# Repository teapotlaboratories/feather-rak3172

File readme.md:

# Teapotlabs Feather RAK3172

Teapotlabs Feather RAK3172 a Low-cost, Low-power LoRaWAN development board that breaks out [RAKwireless RAK3172](https://docs.rakwireless.com/Product-Categories/WisDuo/RAK3172-Module/Datasheet) to an Adafruit Feather-compatible format.

Based on the RAK3172, a STM32WLE5CC based module with ARM Cortex M4 processor, 48 MHz and 3.3V logic. The chip has a 256K of flash and 64K of RAM. 
With low-power application in mind, the board is capable to be in sleep mode for as low as 11uA, it also has a built-in voltage divider to sense battery voltage and battery charger.

Teapotlabs Feather RAK3172 is heavily inspired by [Penguino STM32WL LoRa-E5](https://github.com/azerimaker/Penguino-STM32WL-LoRa-E5) and [BastWAN-WLE](https://github.com/ElectronicCats/BastWAN-WLE) projects!

## Specification

- [RAK3172](https://docs.rakwireless.com/Product-Categories/WisDuo/RAK3172-Module/Overview/): An STM32WLE5CC module
- 3.3V only power/pin. 
- Down to 11uA Deep-Sleep
- Switchable TX Power. 14 dBm or 22 dBm on 915MHz frequency
- Supports LoRaWAN 1.0.3
- USB-C for **Arduino** and  **Mbed OS/STM32Cube** programming
- SMA antenna connector 
- JST-PH 2-Pin Battery Connector
- Built-in LiPo Charger ( 200mA Charge Rate )
- Voltage-Divider for Battery Monitoring ( default: **disabled** )
- LED Indicator on pin 8 ( default: **disabled** )
- Compatible with many Adafruit FeatherWings
- Max 1A power output

## To-do
- Update assembly/TeapotFeatherRAK3172_Assembly.zip and docs file to Revision 9.1

## Schematics

### Jumper Definition
- JP1 and JP4: Enable/Disable Voltage Divider for Battery Sensing
- JP2: Enable/Disable LED Indicator on Pin 8
- JP3, JP5, and JP6: Enable/Disable UART Bridge

### Revision
- Revision 9  : First public release
- Revision 9.1: Fix LED D1 polarity 

### Pinout Diagram
> :warning: **The following pinout is not complete, please see STM32WLE5CC datasheet for more details.** 

## Board
<p align="center">  <br><b>PCB Render</b></p>

Built using KiCAD, the board is design to be as small as possible. The following design are based on the latest revision.
| Top Board | Bottom Board |
|--|--|
|  |  |
|  |  |

 <p align="center"> <br><b>PCB Top and Bottom Layout</b></p> 
  
### Case

The case is design by [atmakers](https://www.thingiverse.com/atmakers/designs) with **Attribution-ShareAlike 3.0 Unported (CC BY-SA 3.0)** license.
The cases are 3D printable with any generic 3D printer with/without suppport (depends on the orientation). The STL files are available from authors download page  [here](https://www.thingiverse.com/thing:3212895) or from [this](https://github.com/teapotlaboratories/feather-rak3172/tree/main/hardware/case) repo.
 <p align="center"><br><b>Case Open</b></p>
 
### Measurement
Power consumption measured using [Nordic PPK2](https://www.nordicsemi.com/Products/Development-hardware/Power-Profiler-Kit-2). The following are the summary of the measurement:
- Sleep and all jumper disabled (JP1 - JP6): **10.44 uA**
- Sleep and UART-Bridge enabled ( JP3, JP5, and JP6 ): **23.76 uA**
- Sleep, UART-Bridge and Battery Sense enabled ( JP1, and JP3 - JP6 ): **25.41 uA** 
- Transmit at 14 dBm: **40.45 mA**
- Transmit at 20 dBm: **100.38 mA**

More detailed measurement can be found [here](https://github.com/teapotlaboratories/feather-rak3172/tree/main/docs/measurement)

### Bill Of Materials
Most of the components are generic and can be bought from any electornics/semi-conductor distributor. RAK3172 is the only component available in [RAKwireless store](https://store.rakwireless.com/products/wisduo-lpwan-module-rak3172?variant=40014759493830). The bill of materials can be downloaded [here](https://github.com/teapotlaboratories/feather-rak3172/raw/main/hardware/bill_of_materials.csv)

> :warning: **Be sure to buy the RAK3172 variant without IPEX to use SMA connector** 

|Id|Designator|Quantity|Value|Footprint|
|:----|:----|:----|:----|:----|
|1|C11,C7,C4,C1|4|100n|0603_1608Metric|
|2|C6,C3|2|10u|0603_1608Metric|
|3|C9,C8,C10|3|10u|0805_2012Metric|
|4|D1|1|BLUE|0603_1608Metric|
|5|D2|1|ORANGE|0603_1608Metric|
|6|D3|1|B5819W|SOD-123|
|7|J3|1|U262-161N-4BVC11|USB_C_Receptacle_XKB_U262-16XN-4BVC11|
|8|J4|1|SMA-KE-P903|SMA-KE-P903|
|9|J6|1|S2B-PH-SM4-TB|JST_PH_S2B-PH-SM4-TB_1x02-1MP_P2.00mm_Horizontal|
|10|L1|1|0|0402_1005Metric|
|11|Q1|1|DMG3415UQ-7|SOT-23|
|12|R10|1|10M|0603_1608Metric|
|13|R2,R6,R1|3|1k|0603_1608Metric|
|14|R3,R5,R4|3|5.1k|0603_1608Metric|
|15|R7,R8|2|10k|0603_1608Metric|
|16|R9|1|4.7M|0603_1608Metric|
|17|SW1|1|B3U-1000P|SW_SPST_B3U-1000P|
|18|SW2|1|B3U-1000P|SW_SPST_B3U-1000P|
|19|U1|1|RAK3172|RAK3172|
|20|U2|1|CH340E|MSOP-10_3x3mm_P0.5mm|
|21|U3|1|MCP73831T-2ACI/OT|SOT-23-5|
|22|U4|1|XC6220B331MR-G|SOT-23-5|
|23|C5,C2|2|DNP|0402_1005Metric|
|24|J2|1|DNP|PinHeader_1x12_P2.54mm_Vertical|
|25|J1|1|DNP|PinHeader_1x16_P2.54mm_Vertical|

## Programming

By default, programming the device can be done over  the **USB-C**. Internally, the USB-C connects to the UART-Bridge that connects to the **UART2** port of the RAK3172. Out of the factory, the RAK3172 chip ships with an **AT firmware** that can be tested by sending AT command via the USB-C.

Using the USB-C, user can program the board using the **Arduino** or **MbedOS/STM32Cube** SDK.
The following are some very good tutorial to start developing with the device:
 - [Communicating with the AT firmware](https://docs.rakwireless.com/Product-Categories/WisDuo/RAK3172-Module/Quickstart/#rak3172-as-a-lora-lorawan-modem-via-at-command)
 - [Programming with Arduino](https://docs.rakwireless.com/Product-Categories/WisDuo/RAK3172-Module/Quickstart/#rak3172-as-a-stand-alone-device-using-rui3)
 - [Programming with STM32Cube](https://docs.rakwireless.com/Product-Categories/WisDuo/RAK3172-Module/Low-Level-Development/#rak3172-on-stm32cubeide-with-stm32wl-sdk-v1-0-0)
	 - RAKDAP1 is not needed. Before connecting to **STM32CubeProgrammer**, hold `BOOT` and press `RESET` on the board, to boot to UART bootloader of the RAK3172. After `RESET` button is pressed, `BOOT` button can be released, and the board should be able to connect to the **STM32CubeProgrammer**
 - [Programming with MbedOS](https://github.com/hallard/LoRa-E5-Tiny/blob/main/README.md#compile-and-flash-firmware)
	 - Programming the board can be done **without** using the ST-LINK, it should be simillar to [Programming with STM32Cube](https://docs.rakwireless.com/Product-Categories/WisDuo/RAK3172-Module/Low-Level-Development/#rak3172-on-stm32cubeide-with-stm32wl-sdk-v1-0-0) process.

## Example Project
Teapotlabs Feather RAK3172 is a feather compatible board, and hence is compatible with the many available FeatherWing. The following are some example project that uses FeatherWings.

### Over-engineered Clock 
An over-engineered clock with main purpose to showcase FeatherWings compatibility.
FeatherWings and sensors used:  
- [Ultimate GPS](adafruit.com/product/3133)  
- [Tri-Color E-Ink](adafruit.com/product/4814)  
- [Qwiic Shield](sparkfun.com/products/16790)  
- [BME680](adafruit.com/product/3660)  
- [Modified E-Ink Case](learn.adafruit.com/eink-featherwing-display-stand)

<p align="center">

<br><b>Front and Side View</b></p>

<p align="center">  

<br><b>Back View</b>
</p>
 
## Reference
The project won't be possible without the amazing work from people across the globe. The following are the reference to those awesome projects:

 - [Adafruit Feather RP2040](https://github.com/adafruit/Adafruit-Feather-RP2040-PCB)
 - [Penguino STM32WL LoRa-E5](https://github.com/azerimaker/Penguino-STM32WL-LoRa-E5)
 - [BastWAN-WLE](https://github.com/ElectronicCats/BastWAN-WLE)

## License
The product is open-source! However, some part of library used under **src**, might have it's own license.
Please reach out or create a ticket to report any license violation.

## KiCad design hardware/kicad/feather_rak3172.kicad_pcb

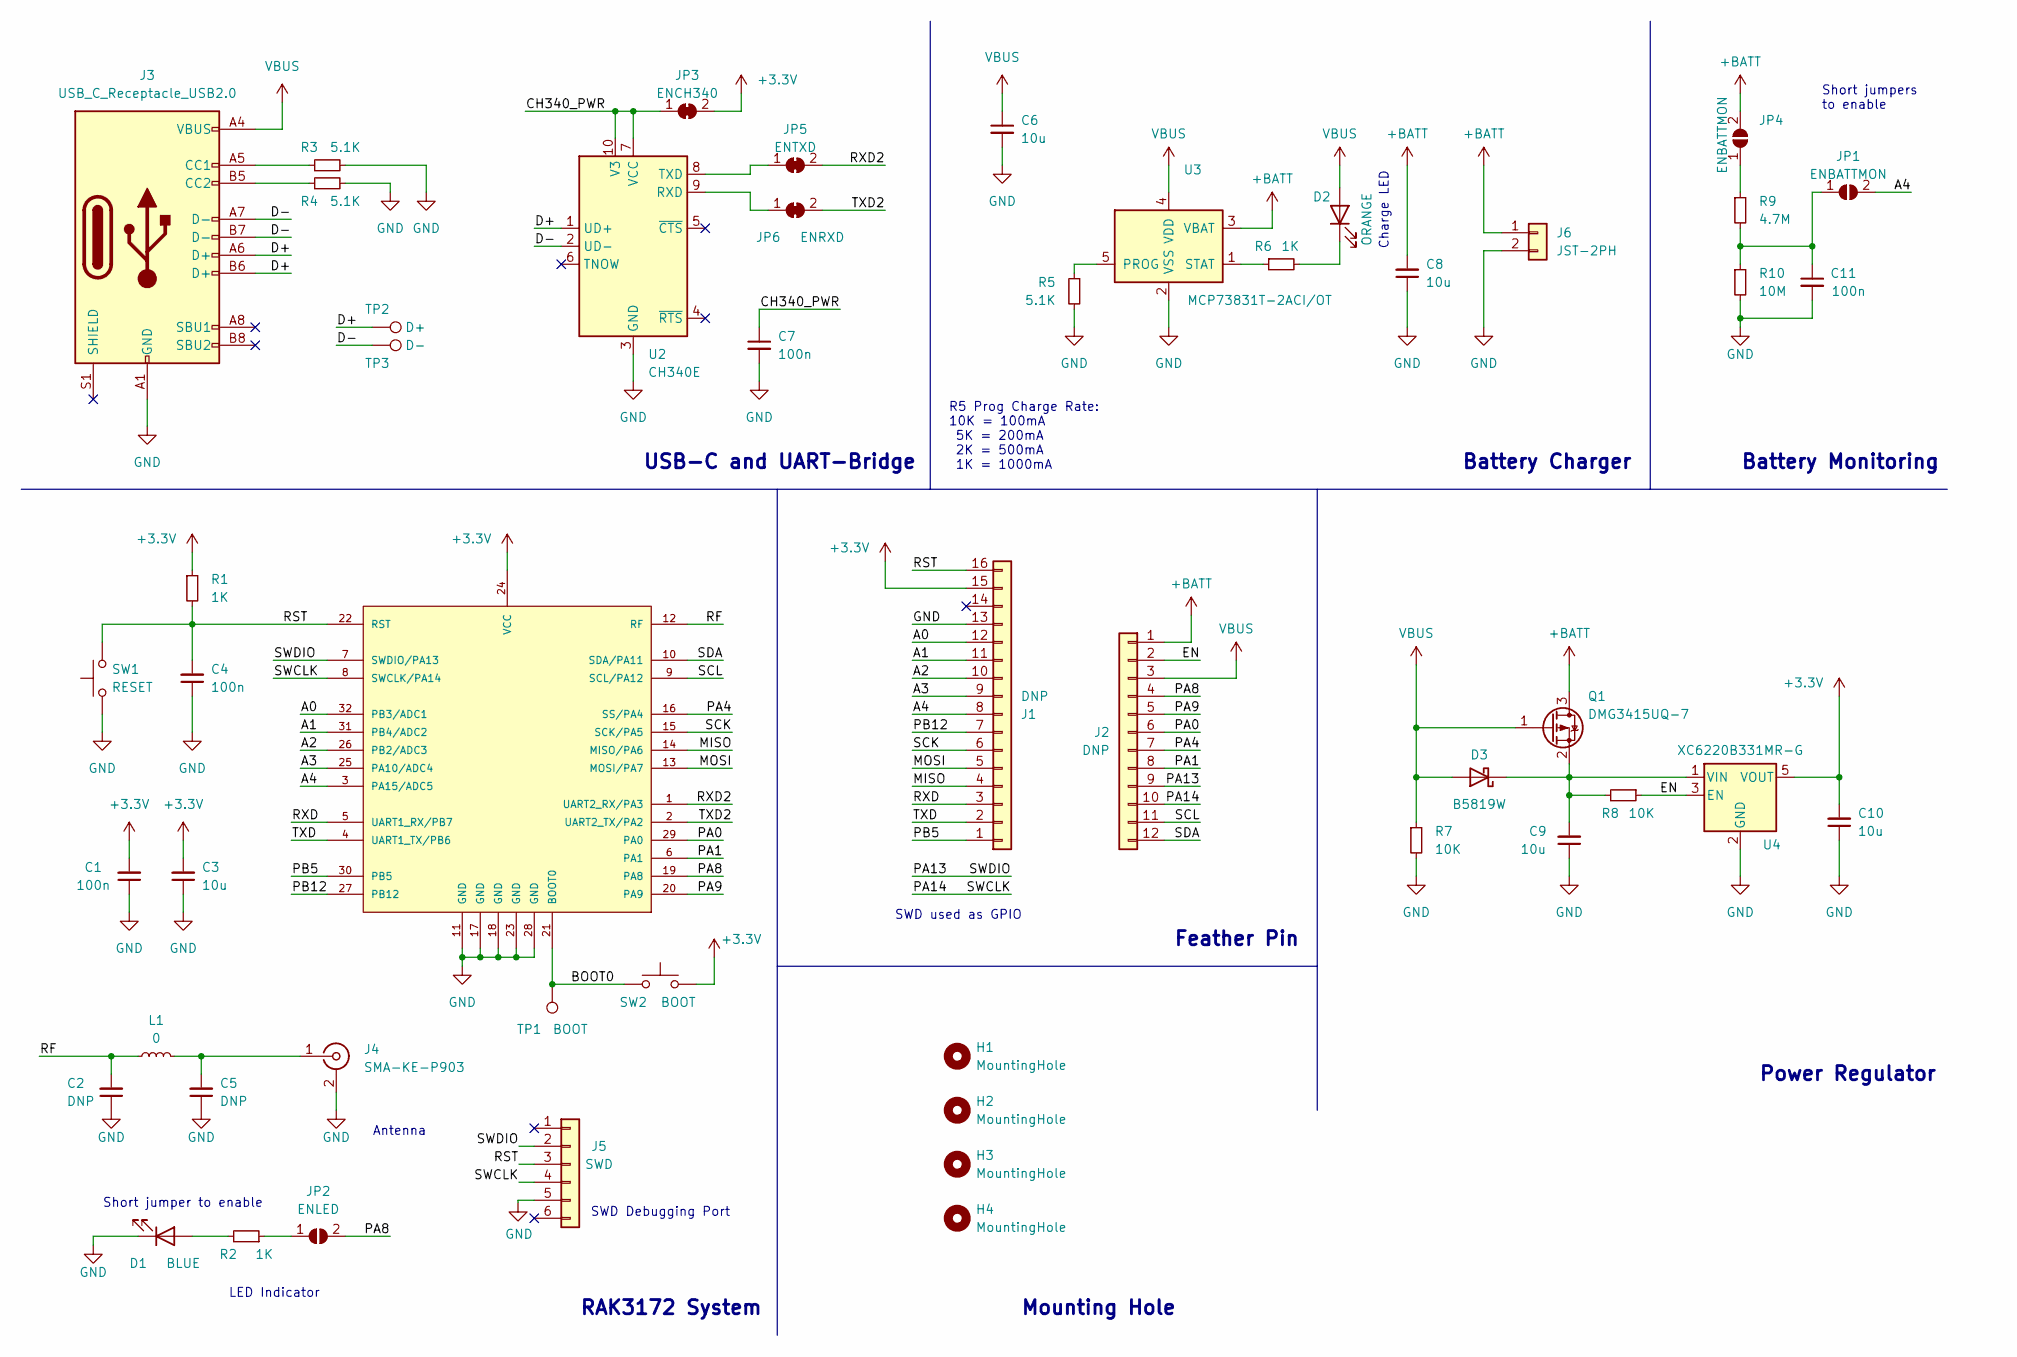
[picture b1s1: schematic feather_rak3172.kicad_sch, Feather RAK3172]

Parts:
C1, C4, C7, C11: 100n; C_0603_1608Metric; Part Description Ceramic Capacitor 100nF 10% 10V X7R
C2, C5: DNP; C_0402_1005Metric
C3, C6: 10u; C_0603_1608Metric; Part Description Ceramic Capacitor 10uF 10% 10V X5R
C8, C9, C10: 10u; C_0805_2012Metric; Part Description Ceramic Capacitor 10uF 10% 10V X5R
D1: BLUE; LED_0603_1608Metric; Part Description Blue 2V 25mA
D2: ORANGE; LED_0603_1608Metric; Part Number Orange 2V 25mA
D3: B5819W; D_SOD-123; Part Description 0.05mA@40V 0.58V@1A
H1, H2, H3, H4: MountingHole; MountingHole_2.5mm
J1: DNP; PinHeader_1x16_P2.54mm_Vertical
J2: DNP; PinHeader_1x12_P2.54mm_Vertical
J3: USB_C_Receptacle_USB2.0; USB_C_Receptacle_XKB_U262-16XN-4BVC11; Part Number U262-161N-4BVC11
J4: SMA-KE-P903; Part Number SMA-KE-P903
J5: SWD; Tag-Connect_TC2030-IDC-NL_2x03_P1.27mm_Vertical
J6: JST-2PH; JST_PH_S2B-PH-SM4-TB_1x02-1MP_P2.00mm_Horizontal; Part Number JST-PH S2B-PH-SM4-TB
JP1, JP4: ENBATTMON; SolderJumper-2_P1.3mm_Open_RoundedPad1.0x1.5mm
JP2: ENLED; SolderJumper-2_P1.3mm_Open_RoundedPad1.0x1.5mm
JP3: ENCH340; SolderJumper-2_P1.3mm_Bridged_RoundedPad1.0x1.5mm
JP5: ENTXD; SolderJumper-2_P1.3mm_Bridged_RoundedPad1.0x1.5mm
JP6: ENRXD; SolderJumper-2_P1.3mm_Bridged_RoundedPad1.0x1.5mm
L1: 0; L_0402_1005Metric
Q1: DMG3415UQ-7; SOT-23; Part Number DMG3415UQ-7
R1, R2, R6: 1K; R_0603_1608Metric; Part Description Resistor 1k 5% 100mW
R3, R4: 5.1K; R_0603_1608Metric; Part Description Resistor 5.1K 1% 100mW
R5: 5.1K; R_0603_1608Metric; Part Description Resistor 5.1k 1% 100mW
R7, R8: 10K; R_0603_1608Metric; Part Description Resistor 10k 5% 100mW
R9: 4.7M; R_0603_1608Metric; Part Description Resistor 4.7M 1% 100mW
R10: 10M; R_0603_1608Metric; Part Description Resistor 10M 1% 100mW
SW1: RESET; SW_SPST_B3U-1000P; Part Number B3U-1000P
SW2: BOOT; SW_SPST_B3U-1000P; Part Number B3U-1000P
TP1: BOOT; TestPoint_Pad_D1.0mm
TP2: D+; TestPoint_Pad_D1.0mm
TP3: D-; TestPoint_Pad_D1.0mm
U1: RAK3172; Part Number RAK3172
U2: CH340E; MSOP-10_3x3mm_P0.5mm; Part Number CH340E
U3: MCP73831T-2ACI/OT; SOT-23-5; Part Number MCP73831T-2ACI/OT
U4: XC6220B331MR-G; SOT-23-5; Part Number XC6220B331MR-G

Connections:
+3.3V: C1.2, C3.2, C10.2, J1.15, JP3.2 (B), R1.1, SW2.1, U1.24 (VCC), U4.5 (VOUT)
+BATT: C8.2, J2.1, J6.1, JP4.2 (B), Q1.3 (D), U3.3 (VBAT)
/A0: J1.12, U1.32 (PB3/ADC1)
/A1: J1.11, U1.31 (PB4/ADC2)
/A2: J1.10, U1.26 (PB2/ADC3)
/A3: J1.9, U1.25 (PA10/ADC4)
/A4: J1.8, JP1.2 (B), U1.3 (PA15/ADC5)
/BOOT0: SW2.2, TP1.1, U1.21 (BOOT0)
/CH340_PWR: C7.1, JP3.1 (A), U2.7 (VCC), U2.10 (V3)
/D+: J3.A6 (D+), J3.B6 (D+), TP2.1, U2.1 (UD+)
/D-: J3.A7 (D-), J3.B7 (D-), TP3.1, U2.2 (UD-)
/EN: J2.2, R8.1, U4.3 (EN)
/MISO: J1.4, U1.14 (MISO/PA6)
/MOSI: J1.5, U1.13 (MOSI/PA7)
/PA0: J2.6, U1.29 (PA0)
/PA1: J2.8, U1.6 (PA1)
/PA4: J2.7, U1.16 (SS/PA4)
/PA8: J2.4, JP2.2 (B), U1.19 (PA8)
/PA9: J2.5, U1.20 (PA9)
/PA13: J2.9, J5.2, U1.7 (SWDIO/PA13)
/PA14: J2.10, J5.4, U1.8 (SWCLK/PA14)
/PB5: J1.1, U1.30 (PB5)
/PB12: J1.7, U1.27 (PB12)
/RF: C2.2, L1.1, U1.12 (RF)
/RST: C4.2, J1.16, J5.3, R1.2, SW1.2, U1.22 (RST)
/RXD: J1.3, U1.5 (UART1_RX/PB7)
/RXD2: JP5.2 (B), U1.1 (UART2_RX/PA3)
/SCK: J1.6, U1.15 (SCK/PA5)
/SCL: J2.11, U1.9 (SCL/PA12)
/SDA: J2.12, U1.10 (SDA/PA11)
/TXD: J1.2, U1.4 (UART1_TX/PB6)
/TXD2: JP6.2 (B), U1.2 (UART2_TX/PA2)
GND: C1.1, C2.1, C3.1, C4.1, C5.1, C6.2, C7.2, C8.1, C9.1, C10.1, C11.2, D1.1 (K), J1.13, J3.A1 (GND), J3.A12 (GND), J3.B1 (GND), J3.B12 (GND), J4.2 (Ext), J5.5, J6.2, R3.2, R4.2, R5.2, R7.2, R10.2, SW1.1, U1.11 (GND), U1.17 (GND), U1.18 (GND), U1.23 (GND), U1.28 (GND), U2.3 (GND), U3.2 (VSS), U4.2 (GND)
unnamed: C5.2, J4.1 (In), L1.2
unnamed: C9.2, D3.1 (K), Q1.2 (S), R8.2, U4.1 (VIN)
unnamed: C11.1, JP1.1 (A), R9.2, R10.1
unnamed: D2.1 (K), R6.2
unnamed: J3.A5 (CC1), R3.1
unnamed: J3.B5 (CC2), R4.1
unnamed: JP2.1 (A), R2.1
unnamed: JP4.1 (A), R9.1
unnamed: JP5.1 (A), U2.8 (TXD)
unnamed: JP6.1 (A), U2.9 (RXD)
unnamed: D1.2 (A), R2.2
unnamed: R5.1, U3.5 (PROG)
unnamed: R6.1, U3.1 (STAT)
VBUS: C6.1, D2.2 (A), D3.2 (A), J2.3, J3.A4 (VBUS), J3.A9 (VBUS), J3.B4 (VBUS), J3.B9 (VBUS), Q1.1 (G), R7.1, U3.4 (VDD)

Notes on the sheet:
Charge LED
Battery Monitoring
RAK3172 System
SWD used as GPIO
Mounting Hole
R5 Prog Charge Rate: 10K = 100mA 5K = 200mA 2K = 500mA 1K = 1000mA
Short jumpers to enable
Short jumper to enable
USB-C and UART-Bridge
SWD Debugging Port
LED Indicator
Antenna
Power Regulator
Battery Charger
Feather Pin

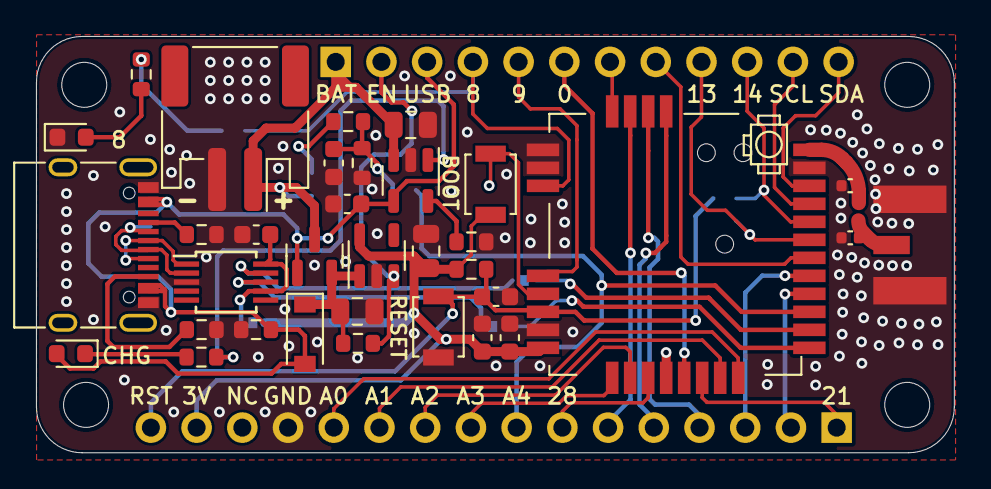
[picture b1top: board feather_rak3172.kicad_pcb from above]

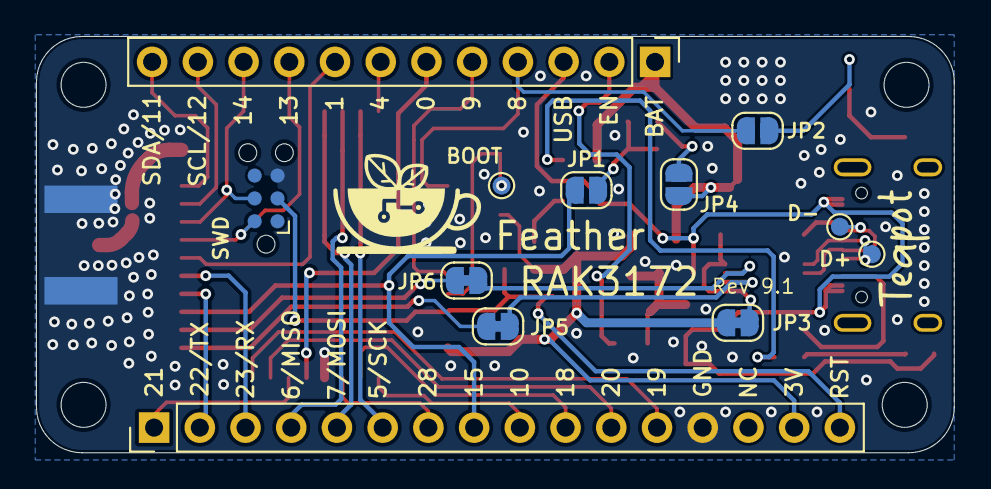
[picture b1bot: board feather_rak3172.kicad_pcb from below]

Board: 2 copper layers, 51.0 x 23.1 mm, 51 parts (12 on the bottom side), 47 nets.

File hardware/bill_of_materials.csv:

Id,Designator,Quantity,Manufacturer,Manufacturer Part Number,Value,Description,Footprint,Type,Distributor,Distributor Part Number,Distributor Link
1,"C11,C7,C4,C1",4,YAGEO,CC0603KRX7R6BB104,100n,Ceramic Capacitor 100n 10% 10V X7R,0603_1608Metric,SMD,LCSC,C519438,https://www.lcsc.com/product-detail/_YAGEO-_C519438.html
2,"C6,C3",2,Samsung Electro-Mechanics,CL10A106KP8NNNC,10u,Ceramic Capacitor 10u 10% 10V X5R,0603_1608Metric,SMD,LCSC,C19702,https://www.lcsc.com/product-detail/_Samsung-Electro-Mechani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
3,"C9,C8,C10",3,Samsung Electro-Mechanics,CL21A106KPFNNNE,10u,Ceramic Capacitor 10u 10% 10V X5R,0805_2012Metric,SMD,LCSC,C17024,https://www.lcsc.com/product-detail/_Samsung-Electro-Mechani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
4,D1,1,Everlight Elec,19-217/BHC-ZL1M2RY/3T,BLUE,LED Blue 2V 25mA,0603_1608Metric,SMD,LCSC,C72041,https://www.lcsc.com/product-detail/_Everlight-Elec-_C72041.html
5,D2,1,EKINGLUX,E6C0603SEAC1UDA,ORANGE,LED Orange 2V 25mA,0603_1608Metric,SMD,LCSC,C375450,https://www.lcsc.com/product-detail/_EKINGLUX-_C375450.html
6,D3,1,GOODWORK,B5819W,B5819W,Schottky Barrier Diodes (SBD) 40V 0.58V@1A,SOD-123,SMD,LCSC,C2943878,https://www.lcsc.com/product-detail/_GOODWORK-_C2943878.html
7,J3,1,XKB Connectivity,U262-161N-4BVC11,U262-161N-4BVC11,USB Type C Receptacle,USB_C_Receptacle_XKB_U262-16XN-4BVC11,SMD,LCSC,C319148,https://www.lcsc.com/product-detail/_XKB-Connectivity-_C319148.html
8,J4,1,DreamLNK,SMA-KE-P903,SMA-KE-P903,SMA RF Connectors Board Edge 50Ω 5.35mm 915MHz ,SMA-KE-P903,Through-Hole,LCSC,C914558,https://www.lcsc.com/product-detail/_DreamLNK-_C914558.html
9,J6,1,JST Sales America Inc.,S2B-PH-SM4-TB(LF)(SN),S2B-PH-SM4-TB,"Connector Header Right Angle 2 position 0.079"" (2.00mm)",JST_PH_S2B-PH-SM4-TB_1x02-1MP_P2.00mm_Horizontal,SMD,LCSC,C295747,https://www.lcsc.com/product-detail/Wire-To-Board-Wire-To-Wi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
10,L1,1,YAGEO,RC0402JR-070RL,0,Resistor 0 5% 65mW,0402_1005Metric,SMD,LCSC,C60485,https://www.lcsc.com/product-detail/_YAGEO-_C60485.html
11,Q1,1,Diodes Incorporated,DMG3415UQ-7,DMG3415UQ-7,MOSFET P-Channel 20V 4A 39mΩ@4.5V,SOT-23,SMD,LCSC,C459537,https://www.lcsc.com/product-detail/_Diodes-Incorporated-_C4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
12,R10,1,UNI-ROYAL(Uniroyal Elec),0603WAF1005T5E,10M,Resistor 10M 1% 100mW,0603_1608Metric,SMD,LCSC,C7250,https://www.lcsc.com/product-detail/_UNI-ROYAL-Uniroyal-Elec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
13,"R2,R6,R1",3,FOJAN,FRC0603J102 TS,1k,Resistor 1k 5% 100mW,0603_1608Metric,SMD,LCSC,C2907113,https://www.lcsc.com/product-detail/_FOJAN-_C2907113.html
14,"R3,R5,R4",3,YAGEO,RC0603FR-075K1L,5.1k,Resistor 5.1k 1% 100mW,0603_1608Metric,SMD,LCSC,C105580,https://www.lcsc.com/product-detail/_YAGEO-_C105580.html
15,"R7,R8",2,YAGEO,RC0603JR-0710KL,10k,Resistor 10k 5% 100mW,0603_1608Metric,SMD,LCSC,C99198,https://www.lcsc.com/product-detail/_YAGEO-_C99198.html
16,R9,1,UNI-ROYAL(Uniroyal Elec),0603WAF4704T5E,4.7M,Resistor 4.7M 1% 100mW,0603_1608Metric,SMD,LCSC,C23163,https://www.lcsc.com/product-detail/_UNI-ROYAL-Uniroyal-Elec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
17,SW1,1,Omron Electronics,B3U-1000P,B3U-1000P,Tactile Switches SPST 50mA 12V 2.5x3mm,SW_SPST_B3U-1000P,SMD,LCSC,C231329,https://www.lcsc.com/product-detail/_Omron-Electronics-_C231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
18,SW2,1,Omron Electronics,B3U-1000P,B3U-1000P,Tactile Switches SPST 50mA 12V 2.5x3mm,SW_SPST_B3U-1000P,SMD,LCSC,C231329,https://www.lcsc.com/product-detail/_Omron-Electronics-_C231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
19,U1,1,RAKwireless,RAK3172,RAK3172,RAK3172 Module without IPEX AS923,RAK3172,SMD,RAKwireless,309044,Contact inquiry@rakwireless.com for SKU: 309044
20,U2,1,WCH(Jiangsu Qin Heng),CH340E,CH340E,USB to UART IC 2Mbps Transceiver USB 2.0,MSOP-10_3x3mm_P0.5mm,SMD,LCSC,C99652,https://www.lcsc.com/product-detail/_WCH-Jiangsu-Qin-Heng-_C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
21,U3,1,Microchip Technology,MCP73831T-2ACI/OT,MCP73831T-2ACI/OT,Charger IC Lithium Ion/Polymer,SOT-23-5,SMD,LCSC,C424093,https://www.lcsc.com/product-detail/Battery-Management-ICs_M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
22,U4,1,Torex Semiconductor,XC6220B331MR-G,XC6220B331MR-G,Linear Voltage Regulators (LDO) 1A Fixed +3.3V,SOT-23-5,SMD,LCSC,C86534,https://www.lcsc.com/product-detail/_Torex-Semicon-_C86534.html
23,"C5,C2",2,-,-,DNP,Do Not Populate,0402_1005Metric,DNP,-,-,-
24,J2,1,-,-,DNP,Do Not Populate,PinHeader_1x12_P2.54mm_Vertical,DNP,-,-,-
25,J1,1,-,-,DNP,Do Not Populate,PinHeader_1x16_P2.54mm_Vertical,DNP,-,-,-

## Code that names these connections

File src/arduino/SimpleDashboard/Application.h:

#ifndef TEAPOT_APPLICATION_H
#define TEAPOT_APPLICATION_H

#include "Arduino.h"
#include "Adafruit_BME680.h"
#include "TinyGPSPlus.h"

// configuration for teapot bwlr3d application
#include "Configuration.h"

/* pin definition */
#define BLUE_LED      PA8
//#define GPS_ENABLE            nullptr
//#define GPS_RESET            nullptr
#define BATT_MEASURE  PA15
#define GPS_TXD       PB7
#define GPS_RXD       PB6
#define I2C_SDA       PA11
#define I2C_SCL       PA12

#ifndef ADC_TO_BATTERY
  #error "ADC_TO_BATTERY not set"
#endif

/* application definition */
namespace teapot{
  enum class ReturnCode {
    kOk = 0,
    kError,
    kBme68xNotFound,
    kBme68xReadFail,
    kPeripheralOff,
    kTimeout,
  };
  
  enum class Sensor : uint32_t {
    kNone     = 0b0,
    kAll      = 0b1111,
    kBme68x   = 0b1,
  };
  uint32_t operator|( const Sensor m, const Sensor n );  
  uint32_t operator&( const uint32_t m, const Sensor n );  
  
  struct SensorData {
    // Temperature (Celsius)
    float temperature;
    // Pressure (hPascals)
    uint32_t pressure;
    // Humidity (RH %)
    float humidity;
    // Gas resistor (ohms)
    uint32_t gas_resistance;
  };

  class Application {
    private:
      Adafruit_BME680   bme68x;
      TinyGPSPlus       l86;
      bool              enable_peripheral;
      
      void  SetupBme68x();
    public:
      Application();
      void          Initialize();
      ReturnCode    ConfigureSensor();
      void          EnablePeripheral( bool enable );
      ReturnCode    EnableLed( bool enable );
      ReturnCode    EnableGnss( bool enable );
      int           ReadBatteryAdc();
      float         ReadBatteryVoltage();
      ReturnCode    GetSensorData( SensorData& data, Sensor sensor_selection = Sensor::kAll );
      void          ResetGnssData();
      ReturnCode    ProcessGnssStream(float hdop, uint32_t sat, unsigned long ms);
      TinyGPSPlus&  GetGnssData();
  };
  
} // namespace teapot


/* lora payload definition */
namespace teapot{
namespace payload {
  /* Payload Component Definition */
  const uint32_t kVersion = 0x01;
  enum class Type {
    kEnvironmentalSensorTypeB = 0x05
  };
  
  struct Header {
    uint8_t version;
    uint8_t type;
  } __attribute__((packed));

  /* Payload Definition */  
  /* environmental payload */
  class EnvironmentalSensorTypeB {
    struct Frame {
      Header header;
      uint16_t temperature;  // Celsius
      uint16_t humidity; // RH %
      uint16_t pressure;  // Pascals
    } __attribute__((packed));
    
    const Type type = teapot::payload::Type::kEnvironmentalSensorTypeB;
    Frame data;
    public:
      EnvironmentalSensorTypeB( 
        uint16_t temperature,
        uint16_t humidity,
        uint16_t pressure
      );
      size_t GetAsBytes(uint8_t* data, size_t size);
  };

} // namespace payload 
} // namespace teapot

#endif // TEAPOT_APPLICATION_H

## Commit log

2022-12-25 add feather template
2022-12-28 initial board design
2022-12-29 push initial board layout
2022-12-31 initial completed wiring
2022-12-31 add additional graphics
2022-12-31 add revision
2023-01-02 add impedance matching circuit and jumper to disable ch340, voltage divider
2023-01-07 breakout D+ and D-, fix incorrect ch340e power wiring, add minor comments
2023-01-07 add more ground stiching
2023-01-18 reduce text thickness
2023-01-18 update 3d model path
2023-01-18 slightly align RF trace with matching circuit
2023-01-19 remove unnecessary ground pour
2023-01-19 revision 4
2023-01-20 minor trace changes
2023-01-20 minor traces adjustment
2023-01-24 minor trace adjustment
2023-01-25 add component description and minor footprint changes
2023-02-07 remove usb-c shield ground connection
2023-02-07 move capacitor closer to charger chip
2023-02-07 minor cosmetic changes
2023-02-07 revision 5
2023-02-11 remove matching circuit, trace too short
2023-02-11 re-add matching circuit, improve rf trace angle
2023-02-20 remove 3v3 signal from swd pinout
2023-02-20 remove gnd via under antenna port
2023-02-20 change antenna part number
2023-02-20 add extra trace to batt pin out
2023-02-22 add solder jump for txd and rxd, minor silkscreen changes
2023-02-22 minor silkscreen changes
2023-02-22 add code example
2023-02-24 add epd driver from lolin
2023-02-24 update example code
2023-03-21 change solder jump to open, and minor component description changes
2023-03-21 update silkscreen version, and minor sch and silkscreen changes
2023-03-21 minor schematic unit changes
2023-03-21 change sma connector to through-hole type
2023-03-21 add library submodule
2023-03-21 fix components position
2023-03-22 change boot button to 3v3
2023-03-22 minor schematic changes
2023-04-23 add documentation files
2023-04-26 add measurement doc
2023-04-26 add assembly file
2023-04-26 add bill of materials
2023-04-26 initial readme
2023-04-26 add readme
2023-04-30 add pinout images
2023-04-30 update pinout diagram
2023-05-22 fix D1 polarity

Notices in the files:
readme.md:
License:
License: MIT
